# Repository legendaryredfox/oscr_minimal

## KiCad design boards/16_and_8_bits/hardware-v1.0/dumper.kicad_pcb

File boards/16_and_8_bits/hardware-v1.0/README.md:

# 16_and_8_bits v1.0

Versão **v1.0** da placa [`16_and_8_bits`](../README.md): shield 100% THT para Arduino Mega 2560 R3, só USB. Versão anterior, mantida ao lado da mais nova.

| | |
|---|---|
| Slots | SNES (62p), NES (72p), Famicom (60p), Mega Drive (64p), todos a 5 V, e GBA (32p, SMD, 1,5 mm) a 3,3 V (regulador U3) |
| Circuitos | Si5351 em header fêmea e PIC12F629 (CIC do SNES) em soquete. |
| Tamanho | 144,1 × 118,0 mm |
| Projeto KiCad | [`hardware-v1.0/`](.) (`dumper.kicad_pro`, `.kicad_sch`, `.kicad_pcb`) |
| Fábrica (JLCPCB) | `../fab/gerbers-v1.0/`, `../fab/dumper-v1.0-jlcpcb.zip` |
| Renders | `render-cima.png`, `render-baixo.png` |
| Estado | Nada montado nem testado com cartucho; revisar o layout no KiCad antes de encomendar |

## Troca de cartucho

O 5V dos slots vai direto do Mega e **não é cortado por software** (o desligamento por software foi retirado, D139). Para trocar o cartucho, **desligue a placa tirando o cabo USB** do Mega; nunca com a USB ligada.

## Proteção de corrente e tensão (D138)

**F1: fusível de vidro 5×20 mm de 500 mA (ação rápida) em suporte de clipes, opcional.** O suporte é de furo passante (Littelfuse série 100 ou equivalente) e o fusível queimado se troca **sem solda**; fica em série com o 5 V que a placa recebe do Mega Um curto no cartucho queima o fusível e protege a placa, o Mega e a porta USB. A queda é de 0,1 a 0,2 V a 200 mA (o SA-1 do SNES continua abaixo de ~5,2 V). **Sem o fusível no suporte a placa fica sem 5 V** (um fio no lugar dele também serve). Ele limita corrente e não protege contra tensão errada.

## Particularidades desta versão

Mínima que funciona, com o fusível F1 (D144).

## Lista de peças

| Referências | Valor | Footprint | Qtd |
|---|---|---|---|
| A1 | Mega2560_R3_Shield | `dumper:Mega2560_R3_Shield` | 1 |
| C1 | 470u/16V | `Capacitor_THT:CP_Radial_D8.0mm_P3.50mm` | 1 |
| C2,C3,C4,C5,C6,C9 | 100n | `Capacitor_THT:C_Disc_D5.0mm_W2.5mm_P5.00mm` | 6 |
| C7,C8 | 1u | `Capacitor_THT:C_Disc_D5.0mm_W2.5mm_P5.00mm` | 2 |
| D1 | LED 3mm | `LED_THT:LED_D3.0mm` | 1 |
| F1 | Fusivel 5x20 500mA | `Fuse:Fuseholder_Littelfuse_100_series_5x20mm` | 1 |
| FC1 | FC_Slot | `dumper:FC_Slot` | 1 |
| FLG1,FLG2 | PWR_FLAG | `` | 2 |
| GBA1 | GBA_Slot | `dumper:GBA_Slot` | 1 |
| MD1 | MD_Slot | `dumper:MD_Slot` | 1 |
| NES1 | NES_Slot | `dumper:NES_Slot` | 1 |
| R1 | 220R | `Resistor_THT:R_Axial_DIN0207_L6.3mm_D2.5mm_P10.16mm_Horizontal` | 1 |
| R2 | 1k | `Resistor_THT:R_Axial_DIN0207_L6.3mm_D2.5mm_P10.16mm_Horizontal` | 1 |
| SNES1 | SNES_Slot | `dumper:SNES_Slot` | 1 |
| U1 | Si5351_Module | `Connector_PinSocket_2.54mm:PinSocket_1x07_P2.54mm_Vertical` | 1 |
| U2 | PIC12F629 (snescic-lock-resync) | `Package_DIP:DIP-8_W7.62mm_Socket` | 1 |
| U3 | MCP1700-3302E/TO (3,3 V) | `Package_TO_SOT_THT:TO-92` | 1 |

Gerada do esquemático desta versão (`kicad-cli sch export bom`). Peças marcadas DNP ou opcionais: `docs/bom.md` da placa.

## Verificação e fábrica (da raiz do repositório)

```
python3 tools/check_netlist.py --board 16_and_8_bits boards/16_and_8_bits/hardware-v1.0/dumper.kicad_sch
kicad-cli sch erc boards/16_and_8_bits/hardware-v1.0/dumper.kicad_sch
kicad-cli pcb drc boards/16_and_8_bits/hardware-v1.0/dumper.kicad_pcb
tools/export_fab.sh 16_and_8_bits v1.0
tools/render_board.sh 16_and_8_bits v1.0 v1.1
```

Mais: [README da placa](../README.md), [`docs/`](../docs/).

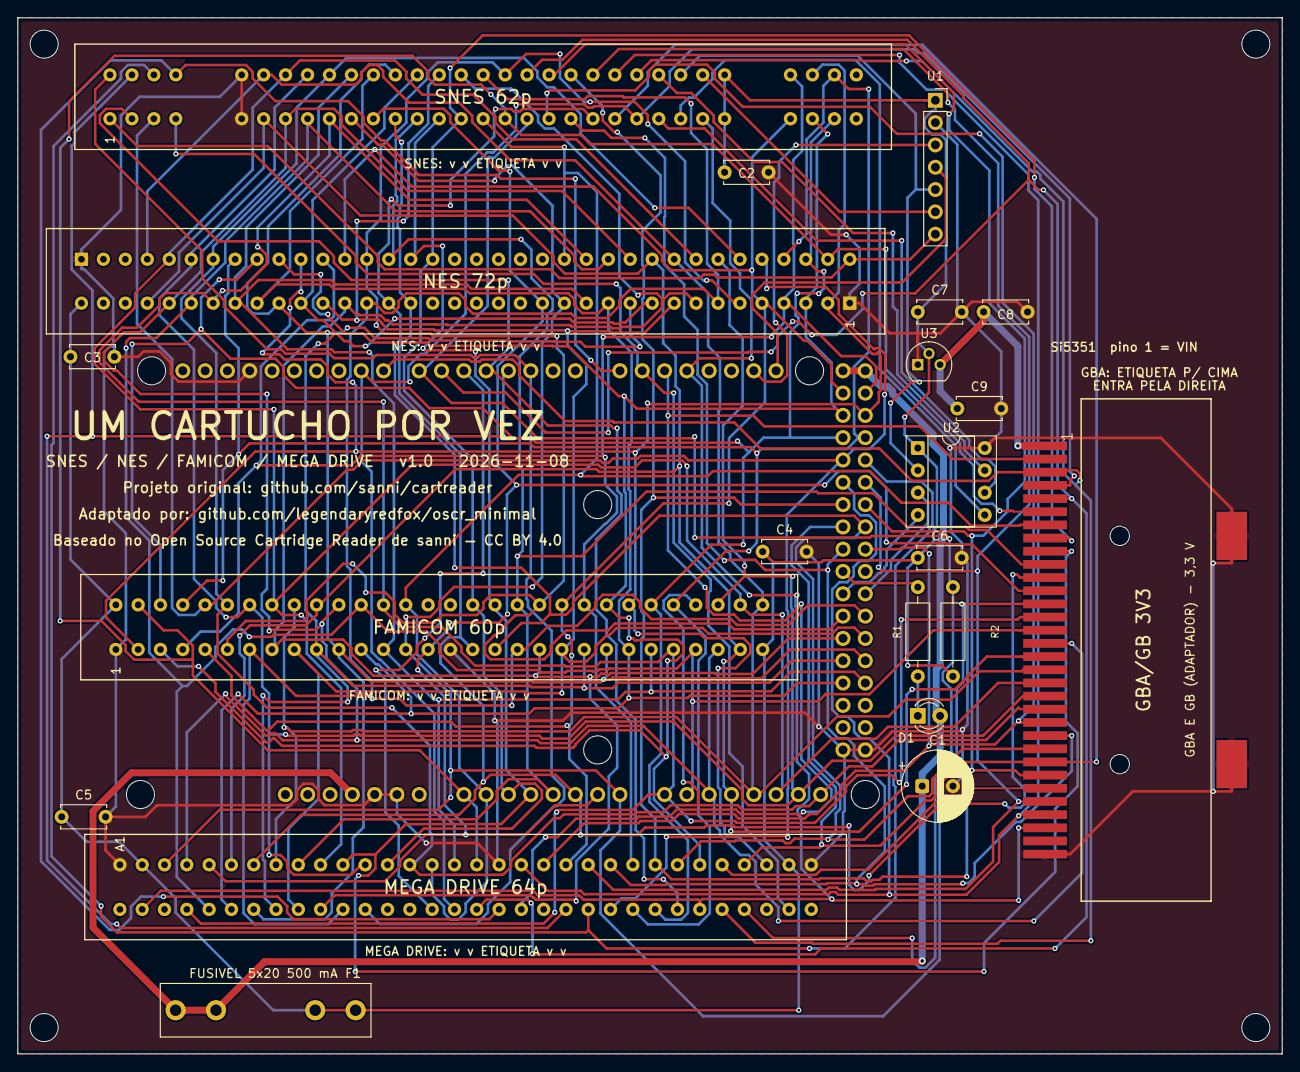
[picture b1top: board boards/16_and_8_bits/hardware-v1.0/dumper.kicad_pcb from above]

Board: 2 copper layers, 144.0 x 118.0 mm, 26 parts (0 on the bottom side), 68 nets.

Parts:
A1: Mega2560_R3_Shield
C1: 470u/16V; CP_Radial_D8.0mm_P3.50mm
C2, C3, C4, C5, C6, C9: 100n; C_Disc_D5.0mm_W2.5mm_P5.00mm
C7, C8: 1u; C_Disc_D5.0mm_W2.5mm_P5.00mm
D1: LED 3mm; LED_D3.0mm
F1: Fusivel 5x20 500mA; Fuseholder_Littelfuse_100_series_5x20mm
FC1: FC_Slot
GBA1: GBA_Slot
MD1: MD_Slot
MH1, MH2, MH3, MH4: MountingHole_3.2mm; MountingHole_3.2mm_M3
NES1: NES_Slot
R1: 220R; R_Axial_DIN0207_L6.3mm_D2.5mm_P10.16mm_Horizontal
R2: 1k; R_Axial_DIN0207_L6.3mm_D2.5mm_P10.16mm_Horizontal
SNES1: SNES_Slot
U1: Si5351_Module; PinSocket_1x07_P2.54mm_Vertical
U2: PIC12F629 (snescic-lock-resync); DIP-8_W7.62mm_Socket
U3: MCP1700-3302E/TO (3,3 V); TO-92

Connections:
+3V3: C8.1, C9.1, GBA1.1, U3.3
+5V: A1.5V1, A1.5V3, A1.5V4, C1.1, D1.2, F1.1
+5V_CART: C2.1, C3.1, C4.1, C5.1, C6.1, C7.1, F1.2, FC1.30, FC1.31, MD1.A2, MD1.A31, NES1.36, R2.1, SNES1.27, SNES1.58, U1.1, U2.1, U3.2
/A0: A1.A0, FC1.32, GBA1.6, MD1.A17, NES1.38, SNES1.17
/A1: A1.A1, FC1.44, GBA1.7, MD1.A15, NES1.50, SNES1.16
/A2: A1.A2, FC1.47, GBA1.8, MD1.A13, NES1.56, SNES1.15
/A3: A1.A3, FC1.48, GBA1.9, MD1.A11, NES1.57, SNES1.14
/A4: A1.A4, FC1.49, GBA1.10, MD1.A9, NES1.58, SNES1.13
/A5: A1.A5, FC1.17, GBA1.11, MD1.A7, NES1.21, SNES1.12
/A6: A1.A6, FC1.15, GBA1.12, MD1.A5, NES1.15, SNES1.11
/A7: A1.A7, FC1.14, GBA1.13, MD1.A3, NES1.14, SNES1.10
/A8: A1.A8, FC1.26, FC1.43, GBA1.14, MD1.B4, NES1.30, NES1.49, SNES1.9
/A9: A1.A9, FC1.27, FC1.42, GBA1.15, MD1.B5, NES1.31, NES1.48, SNES1.8
/A10: A1.A10, FC1.28, FC1.41, GBA1.16, MD1.A4, NES1.32, NES1.47, SNES1.7
/A11: A1.A11, FC1.29, FC1.40, GBA1.17, MD1.A6, NES1.33, NES1.46, SNES1.6
/A12: A1.A12, FC1.39, FC1.60, GBA1.18, MD1.A8, NES1.45, NES1.69, SNES1.37
/A13: A1.A13, FC1.38, FC1.59, GBA1.19, MD1.A10, NES1.44, NES1.68, SNES1.38
/A14: A1.A14, FC1.37, FC1.58, GBA1.20, MD1.A12, NES1.43, NES1.67, SNES1.39
/A15: A1.A15, FC1.36, FC1.57, GBA1.21, MD1.A14, NES1.42, NES1.66, SNES1.40
/CIC_DATA_0: SNES1.55, U2.7
/CIC_DATA_1: SNES1.24, U2.6
/CIC_RESET: SNES1.25, U2.5
/CLK0: NES1.37, SNES1.1, U1.7
/CLK1: SNES1.57, U1.6
/CLK2: SNES1.56, U1.5, U2.2
/D2: A1.D2, MD1.B12, SNES1.32
/D3: A1.D3, MD1.B21, SNES1.33
/D4: A1.D4, MD1.B26, SNES1.2
/D5: A1.D5, MD1.B15
/D6: A1.D6, GBA1.5, MD1.B17, SNES1.49
/D7: A1.D7, MD1.B29, R2.2, SNES1.18
/D8: A1.D8, GBA1.3, MD1.B28, SNES1.54
/D9: A1.D9, GBA1.4, MD1.B16, SNES1.23
/D14: A1.D14, MD1.B18, SNES1.35
/D15: A1.D15, MD1.B31, SNES1.4
/D16: A1.D16, GBA1.2, MD1.B19
/D17: A1.D17, GBA1.30, MD1.B2, MD1.B27, SNES1.26
/D22: A1.D22, FC1.5, FC1.51, MD1.A21, NES1.5, NES1.60, SNES1.28
/D23: A1.D23, FC1.4, FC1.52, MD1.A24, NES1.4, NES1.61, SNES1.59
/D24: A1.D24, FC1.3, FC1.53, MD1.A27, NES1.3, NES1.63, SNES1.29
/D25: A1.D25, FC1.2, FC1.54, MD1.A30, NES1.2, NES1.62, SNES1.60
/D26: A1.D26, FC1.33, FC1.55, MD1.B25, NES1.39, NES1.64, SNES1.30
/D27: A1.D27, FC1.34, FC1.56, MD1.B24, NES1.40, NES1.65, SNES1.61
/D28: A1.D28, FC1.35, MD1.B23, NES1.41, SNES1.3
/D29: A1.D29, MD1.B22, SNES1.34
/D30: A1.D30, GBA1.29, MD1.A19, SNES1.53
/D31: A1.D31, GBA1.28, MD1.A22, SNES1.52
/D32: A1.D32, GBA1.27, MD1.A25, SNES1.51
/D33: A1.D33, GBA1.26, MD1.A28, SNES1.50
/D34: A1.D34, GBA1.25, MD1.A29, SNES1.22
/D35: A1.D35, FC1.18, GBA1.24, MD1.A26, NES1.22, SNES1.21
/D36: A1.D36, GBA1.23, MD1.A23, SNES1.20
/D37: A1.D37, GBA1.22, MD1.A20, SNES1.19
/D42: A1.D42, FC1.6, FC1.50, NES1.6, NES1.59, SNES1.48
/D43: A1.D43, FC1.7, FC1.19, MD1.B11, NES1.7, NES1.23, SNES1.47
/D44: A1.D44, FC1.8, FC1.20, MD1.B10, NES1.8, NES1.24, SNES1.46
/D45: A1.D45, FC1.9, FC1.21, MD1.B9, NES1.9, NES1.25, SNES1.45
/D46: A1.D46, FC1.10, FC1.22, MD1.B8, NES1.10, NES1.26, SNES1.44
/D47: A1.D47, FC1.11, FC1.23, MD1.B7, NES1.11, NES1.27, SNES1.43
/D48: A1.D48, FC1.12, FC1.24, MD1.B6, NES1.12, NES1.28, SNES1.42
/D49: A1.D49, FC1.13, FC1.25, MD1.A16, NES1.13, NES1.29, SNES1.41
GND: A1.GND1, A1.GND2, A1.GND3, A1.GND5, A1.GND6, C1.2, C2.2, C3.2, C4.2, C5.2, C6.2, C7.2, C8.2, C9.2, FC1.1, FC1.16, GBA1.32, GBA1.SHIELD_3, GBA1.SHIELD_4, MD1.A1, MD1.A18, MD1.A32, NES1.1, NES1.72, SNES1.5, SNES1.36, U1.2, U2.8, U3.1
unnamed: A1.D38, R1.2
unnamed: D1.1, R1.1
unnamed: A1.D21, U1.4
unnamed: A1.D20, U1.3
unnamed: A1.D40, U2.4
unnamed: A1.D41, U2.3

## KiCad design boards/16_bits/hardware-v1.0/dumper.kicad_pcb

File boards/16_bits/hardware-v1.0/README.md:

# 16_bits v1.0

Versão **v1.0** da placa [`16_bits`](../README.md): shield 100% THT para Arduino Mega 2560 R3, só USB. Versão anterior, mantida ao lado da mais nova.

| | |
|---|---|
| Slots | SNES (62p) e Mega Drive (64p), 5 V |
| Circuitos | Si5351 em header fêmea e PIC12F629 (CIC do SNES) em soquete. Sem botão de reset em nenhuma versão (D128). |
| Tamanho | 108,1 × 86,1 mm |
| Projeto KiCad | [`hardware-v1.0/`](.) (`dumper.kicad_pro`, `.kicad_sch`, `.kicad_pcb`) |
| Fábrica (JLCPCB) | `../fab/gerbers-v1.0/`, `../fab/dumper-v1.0-jlcpcb.zip` |
| Renders | `render-cima.png`, `render-baixo.png` |
| Proteção | F1: suporte de fusível 5×20 mm, 500 mA, em série com o 5 V dos slots (acrescentado em 2026-11-09, D144) |
| Estado | A placa encomendada (gerbers de 2026-11-03, sem o F1) chegou e foi montada em 2026-11-27: encaixe no Mega e footprints dos slots SNES e Mega Drive conferidos pelo usuário (D233). Teste elétrico e com cartucho ainda não feitos |

## Troca de cartucho

O 5V dos slots vai direto do Mega e **não é cortado por software** (o desligamento por software foi retirado, D139). Para trocar o cartucho, **desligue a placa tirando o cabo USB** do Mega; nunca com a USB ligada.

## F1 (D144)

**F1: fusível de vidro 5×20 mm de 500 mA (ação rápida) em suporte de clipes, de furo passante** (Littelfuse série 100 ou equivalente). Fica em série entre o 5 V do Mega e o `+5V_CART` (slots, Si5351, PIC, R2 e capacitores): um curto no cartucho queima o fusível e protege a placa, o Mega e a porta USB. O fusível queimado se troca **sem solda**. **Sem o fusível no suporte a placa fica sem 5 V** (um fio no lugar também serve). Limita corrente; não protege contra tensão errada. Posição: canto de cima, à direita do Si5351, sem aumentar a placa (108,1 × 86,1 mm). **As placas v1.0 já encomendadas em 2026-11-06 não têm o F1**; estes arquivos valem para uma nova encomenda.

## Particularidades desta versão

Antiga `rev2` (D97): alimentação em 0,8 mm, sem resistores série nem TVS nas linhas de controle, sem `/CART` no D50, sem C5, C6 e pontos de teste, sem furos M3 do Mega. A v1.0 original (trilhas de 0,3 mm) foi encomendada pelo usuário em 2026-11-06 e seus gerbers saíram do repositório (D110).

## Lista de peças

| Referências | Valor | Footprint | Qtd |
|---|---|---|---|
| A1 | Mega2560_R3_Shield | `dumper:Mega2560_R3_Shield` | 1 |
| C1 | 470u/16V | `Capacitor_THT:CP_Radial_D8.0mm_P3.50mm` | 1 |
| C2,C3,C4 | 100n | `Capacitor_THT:C_Disc_D5.0mm_W2.5mm_P5.00mm` | 3 |
| D1 | LED 3mm | `LED_THT:LED_D3.0mm` | 1 |
| FLG1,FLG2 | PWR_FLAG | `` | 2 |
| MD1 | MD_Slot | `dumper:MD_Slot` | 1 |
| F1 | Fusivel 5x20 500mA | `Fuse:Fuseholder_Littelfuse_100_series_5x20mm` | 1 |
| R1 | 220R | `Resistor_THT:R_Axial_DIN0207_L6.3mm_D2.5mm_P10.16mm_Horizontal` | 1 |
| R2 | 1k | `Resistor_THT:R_Axial_DIN0207_L6.3mm_D2.5mm_P10.16mm_Horizontal` | 1 |
| SNES1 | SNES_Slot | `dumper:SNES_Slot` | 1 |
| U1 | Si5351_Module | `Connector_PinSocket_2.54mm:PinSocket_1x07_P2.54mm_Vertical` | 1 |
| U2 | PIC12F629 (em soquete; snescic-lock-resync) | `Package_DIP:DIP-8_W7.62mm` | 1 |

Gerada do esquemático desta versão (`kicad-cli sch export bom`). Peças marcadas DNP ou opcionais: `docs/bom.md` da placa.

## Verificação e fábrica (da raiz do repositório)

```
kicad-cli sch erc boards/16_bits/hardware-v1.0/dumper.kicad_sch
kicad-cli pcb drc boards/16_bits/hardware-v1.0/dumper.kicad_pcb
tools/export_fab.sh 16_bits v1.0
tools/render_board.sh 16_bits v1.0 v1.2 v1.3
```

`tools/check_netlist.py` não se aplica à v1.0 da `16_bits`: o `pinmap.md` atual inclui C5, C6, D3 a D14 e TP2, que esta versão não tem.

Mais: [README da placa](../README.md), [`docs/`](../docs/). Comparação entre as versões: [`docs/versoes.md`](../docs/versoes.md).

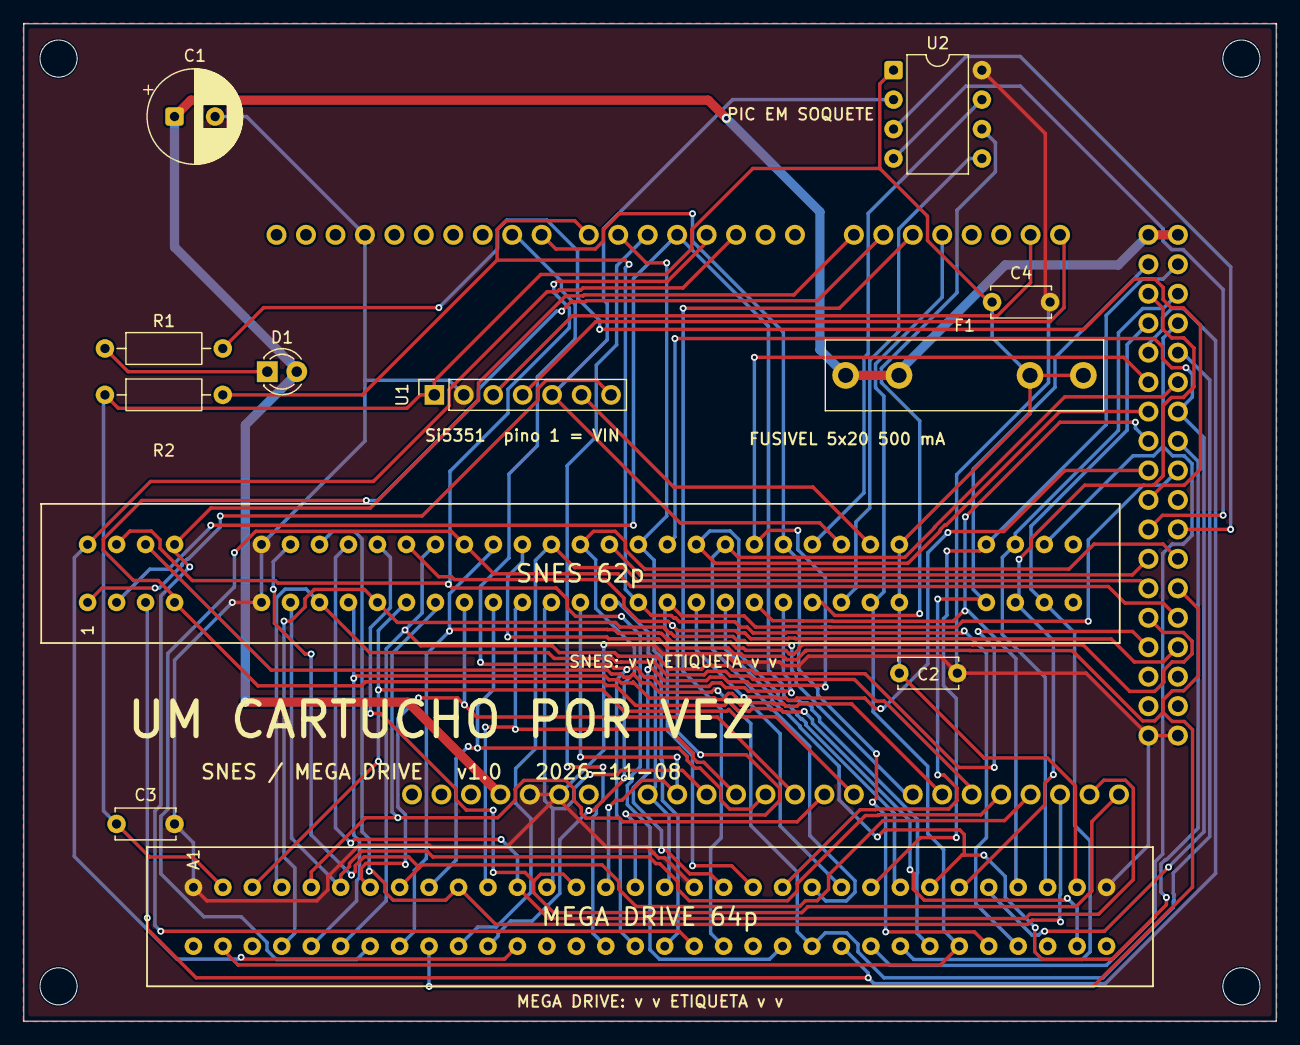
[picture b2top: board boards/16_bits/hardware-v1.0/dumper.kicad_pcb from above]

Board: 2 copper layers, 108.0 x 86.0 mm, 17 parts (0 on the bottom side), 67 nets.

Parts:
A1: Mega2560_R3_Shield
C1: 470u/16V; CP_Radial_D8.0mm_P3.50mm
C2, C3, C4: 100n; C_Disc_D5.0mm_W2.5mm_P5.00mm
D1: LED 3mm; LED_D3.0mm
F1: Fusivel 5x20 500mA; Fuseholder_Littelfuse_100_series_5x20mm
MD1: MD_Slot
MH1, MH2, MH3, MH4: MountingHole_3.2mm; MountingHole_3.2mm_M3
R1: 220R; R_Axial_DIN0207_L6.3mm_D2.5mm_P10.16mm_Horizontal
R2: 1k; R_Axial_DIN0207_L6.3mm_D2.5mm_P10.16mm_Horizontal
SNES1: SNES_Slot
U1: Si5351_Module; PinSocket_1x07_P2.54mm_Vertical
U2: PIC12F629 (em soquete; snescic-lock-resync); DIP-8_W7.62mm

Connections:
+5V: A1.5V1, A1.5V3, A1.5V4, C1.1, D1.2, F1.1
+5V_CART: C2.1, C3.1, C4.1, F1.2, MD1.A2, MD1.A31, R2.1, SNES1.27, SNES1.58, U1.1, U2.1
/A0: A1.A0, MD1.A17, SNES1.17
/A1: A1.A1, MD1.A15, SNES1.16
/A2: A1.A2, MD1.A13, SNES1.15
/A3: A1.A3, MD1.A11, SNES1.14
/A4: A1.A4, MD1.A9, SNES1.13
/A5: A1.A5, MD1.A7, SNES1.12
/A6: A1.A6, MD1.A5, SNES1.11
/A7: A1.A7, MD1.A3, SNES1.10
/A8: A1.A8, MD1.B4, SNES1.9
/A9: A1.A9, MD1.B5, SNES1.8
/A10: A1.A10, MD1.A4, SNES1.7
/A11: A1.A11, MD1.A6, SNES1.6
/A12: A1.A12, MD1.A8, SNES1.37
/A13: A1.A13, MD1.A10, SNES1.38
/A14: A1.A14, MD1.A12, SNES1.39
/A15: A1.A15, MD1.A14, SNES1.40
/CIC_DATA_0: SNES1.55, U2.7
/CIC_DATA_1: SNES1.24, U2.6
/CIC_RESET: SNES1.25, U2.5
/CLK0: SNES1.1, U1.7
/CLK1: SNES1.57, U1.6
/CLK2: SNES1.56, U1.5, U2.2
/D2: A1.D2, MD1.B12, SNES1.32
/D3: A1.D3, MD1.B21, SNES1.33
/D4: A1.D4, MD1.B26, SNES1.2
/D5: A1.D5, MD1.B15
/D6: A1.D6, MD1.B17, SNES1.49
/D7: A1.D7, MD1.B29, R2.2, SNES1.18
/D8: A1.D8, MD1.B28, SNES1.54
/D9: A1.D9, MD1.B16, SNES1.23
/D14: A1.D14, MD1.B18, SNES1.35
/D15: A1.D15, MD1.B31, SNES1.4
/D16: A1.D16, MD1.B19
/D17: A1.D17, MD1.B2, MD1.B27, SNES1.26
/D22: A1.D22, MD1.A21, SNES1.28
/D23: A1.D23, MD1.A24, SNES1.59
/D24: A1.D24, MD1.A27, SNES1.29
/D25: A1.D25, MD1.A30, SNES1.60
/D26: A1.D26, MD1.B25, SNES1.30
/D27: A1.D27, MD1.B24, SNES1.61
/D28: A1.D28, MD1.B23, SNES1.3
/D29: A1.D29, MD1.B22, SNES1.34
/D30: A1.D30, MD1.A19, SNES1.53
/D31: A1.D31, MD1.A22, SNES1.52
/D32: A1.D32, MD1.A25, SNES1.51
/D33: A1.D33, MD1.A28, SNES1.50
/D34: A1.D34, MD1.A29, SNES1.22
/D35: A1.D35, MD1.A26, SNES1.21
/D36: A1.D36, MD1.A23, SNES1.20
/D37: A1.D37, MD1.A20, SNES1.19
/D42: A1.D42, SNES1.48
/D43: A1.D43, MD1.B11, SNES1.47
/D44: A1.D44, MD1.B10, SNES1.46
/D45: A1.D45, MD1.B9, SNES1.45
/D46: A1.D46, MD1.B8, SNES1.44
/D47: A1.D47, MD1.B7, SNES1.43
/D48: A1.D48, MD1.B6, SNES1.42
/D49: A1.D49, MD1.A16, SNES1.41
GND: A1.GND1, A1.GND2, A1.GND3, A1.GND5, A1.GND6, C1.2, C2.2, C3.2, C4.2, MD1.A1, MD1.A18, MD1.A32, SNES1.5, SNES1.36, U1.2, U2.8
unnamed: A1.D38, R1.2
unnamed: D1.1, R1.1
unnamed: A1.D21, U1.4
unnamed: A1.D20, U1.3
unnamed: A1.D40, U2.4
unnamed: A1.D41, U2.3

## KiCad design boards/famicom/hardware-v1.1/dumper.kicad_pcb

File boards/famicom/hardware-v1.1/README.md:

# famicom v1.1

Versão **v1.1** da placa [`famicom`](../README.md): shield 100% THT para Arduino Mega 2560 R3, só USB. Esta é a versão mais nova.

| | |
|---|---|
| Slots | Famicom (60p, 2,54 mm), 5 V |
| Circuitos | Sem Si5351 e sem PIC. |
| Tamanho | 107,1 × 105,1 mm |
| Projeto KiCad | [`hardware-v1.1/`](.) (`dumper.kicad_pro`, `.kicad_sch`, `.kicad_pcb`) |
| Fábrica (JLCPCB) | `../fab/gerbers-v1.1/`, `../fab/dumper-v1.1-jlcpcb.zip` |
| Renders | `render-cima.png`, `render-baixo.png` |
| Estado | Nada montado nem testado com cartucho; revisar o layout no KiCad antes de encomendar |

## Troca de cartucho

O 5V dos slots vai direto do Mega e **não é cortado por software** (o desligamento por software foi retirado, D139). Para trocar o cartucho, **desligue a placa tirando o cabo USB** do Mega; nunca com a USB ligada.

## Proteção de corrente e tensão (D138)

**F1: fusível de vidro 5×20 mm de 500 mA (ação rápida) em suporte de clipes, opcional.** O suporte é de furo passante (Littelfuse série 100 ou equivalente) e o fusível queimado se troca **sem solda**; fica em série com o 5 V que a placa recebe do Mega Um curto no cartucho queima o fusível e protege a placa, o Mega e a porta USB. A queda é de 0,1 a 0,2 V a 200 mA (o SA-1 do SNES continua abaixo de ~5,2 V). **Sem o fusível no suporte a placa fica sem 5 V** (um fio no lugar dele também serve). Ele limita corrente e não protege contra tensão errada.

**Seletor de tensão 3,3 V/5 V dos slots Famicom** (LDO LD1117V33 em TO-220, Q4 de bypass, Q5 de carga, comando no D18; sem resistores em série entre o Mega e os slots, D140). **Padrão: 5 V**; 3,3 V só quando o usuário pede (`--voltage 3v3`, ou o botão da GUI). Passar de 3,3 V para 5 V mostra um alerta e pede confirmação. Os outros slots e o Si5351/PIC ficam direto no 5 V. Cartuchos de 3,3 V ligados em 5 V podem queimar, e em 3,3 V as saídas do Mega continuam em 5 V: **confira a tensão que o cartucho suporta antes de inserir**.

**J1: jumper "TRAVA 3,3 V", opcional.** Fechado, prende o gate do Q4 no 5 V e o slot nunca passa de 3,3 V, mesmo com erro de software ou de GUI: é a única defesa independente do firmware. Aberto, o seletor funciona normalmente.

## O que muda em relação à v1.0

| Peça | Referências | Antes | Agora |
|---|---|---|---|
| 10u/16V | C4 | 0 | 1 |
| TRAVA 3,3 V | J1 | 0 | 1 |
| IRF9540N | Q4 | 0 | 1 |
| 2N7000 | Q5 | 0 | 1 |
| 100k | R9 | 0 | 1 |
| 1k | R10 | 0 | 1 |
| 220R | R11 | 0 | 1 |
| LD1117V33 | U1 | 0 | 1 |
| 100n | C2,C3 | 1 | 2 |

## Lista de peças

| Referências | Valor | Footprint | Qtd |
|---|---|---|---|
| A1 | Mega2560_R3_Shield | `dumper:Mega2560_R3_Shield` | 1 |
| C1 | 470u/16V | `Capacitor_THT:CP_Radial_D8.0mm_P3.50mm` | 1 |
| C2,C3 | 100n | `Capacitor_THT:C_Disc_D5.0mm_W2.5mm_P5.00mm` | 2 |
| C4 | 10u/16V | `Capacitor_THT:CP_Radial_D5.0mm_P2.00mm` | 1 |
| D1 | LED 3mm | `LED_THT:LED_D3.0mm` | 1 |
| F1 | Fusivel 5x20 500mA | `Fuse:Fuseholder_Littelfuse_100_series_5x20mm` | 1 |
| FC1 | FC_Slot | `dumper:FC_Slot` | 1 |
| FLG1,FLG2 | PWR_FLAG | `` | 2 |
| J1 | TRAVA 3,3 V | `Connector_PinHeader_2.54mm:PinHeader_1x02_P2.54mm_Vertical` | 1 |
| Q4 | IRF9540N | `Package_TO_SOT_THT:TO-220-3_Vertical` | 1 |
| Q5 | 2N7000 | `Package_TO_SOT_THT:TO-92_Inline` | 1 |
| R1 | 220R | `Resistor_THT:R_Axial_DIN0207_L6.3mm_D2.5mm_P10.16mm_Horizontal` | 1 |
| R9 | 100k | `Resistor_THT:R_Axial_DIN0204_L3.6mm_D1.6mm_P2.54mm_Vertical` | 1 |
| R10 | 1k | `Resistor_THT:R_Axial_DIN0204_L3.6mm_D1.6mm_P2.54mm_Vertical` | 1 |
| R11 | 220R | `Resistor_THT:R_Axial_DIN0204_L3.6mm_D1.6mm_P2.54mm_Vertical` | 1 |
| U1 | LD1117V33 | `Package_TO_SOT_THT:TO-220-3_Vertical` | 1 |

Gerada do esquemático desta versão (`kicad-cli sch export bom`). Peças marcadas DNP ou opcionais: `docs/bom.md` da placa.

## Verificação e fábrica (da raiz do repositório)

```
python3 tools/check_netlist.py --board famicom boards/famicom/hardware-v1.1/dumper.kicad_sch
kicad-cli sch erc boards/famicom/hardware-v1.1/dumper.kicad_sch
kicad-cli pcb drc boards/famicom/hardware-v1.1/dumper.kicad_pcb
tools/export_fab.sh famicom v1.1
tools/render_board.sh famicom v1.0 v1.1
```

Mais: [README da placa](../README.md), [`docs/`](../docs/).

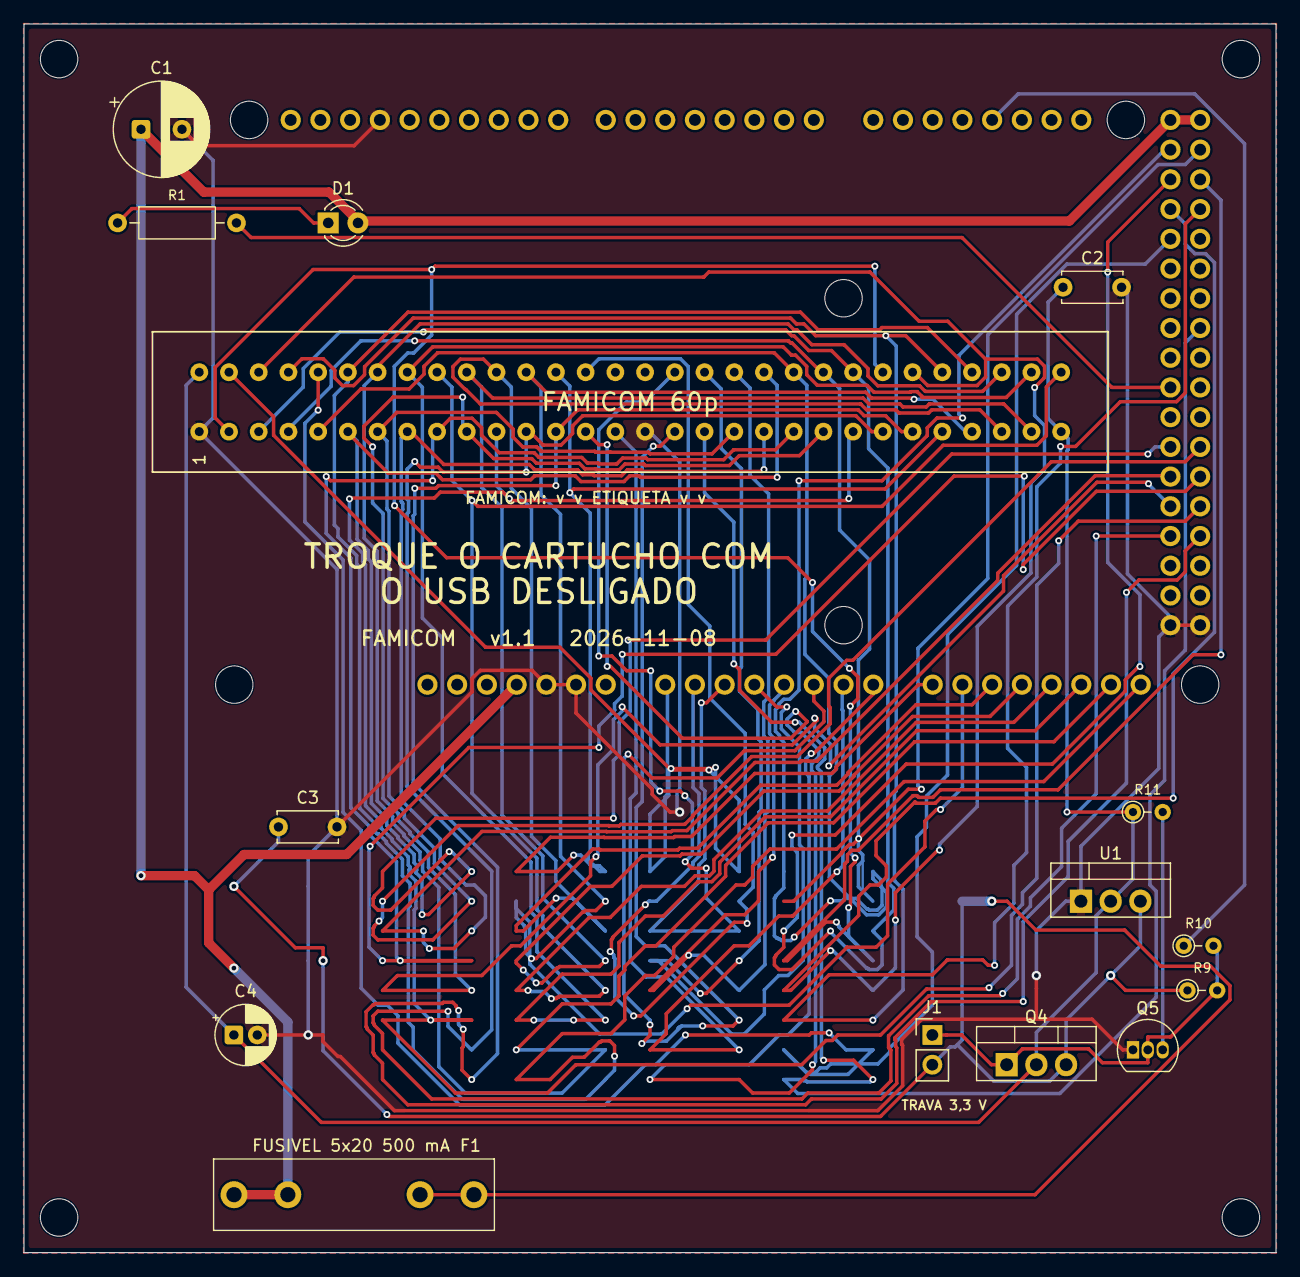
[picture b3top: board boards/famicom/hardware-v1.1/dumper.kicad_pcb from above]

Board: 2 copper layers, 107.0 x 105.0 mm, 20 parts (0 on the bottom side), 41 nets.

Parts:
A1: Mega2560_R3_Shield
C1: 470u/16V; CP_Radial_D8.0mm_P3.50mm
C2, C3: 100n; C_Disc_D5.0mm_W2.5mm_P5.00mm
C4: 10u/16V; CP_Radial_D5.0mm_P2.00mm
D1: LED 3mm; LED_D3.0mm
F1: Fusivel 5x20 500mA; Fuseholder_Littelfuse_100_series_5x20mm
FC1: FC_Slot
J1: TRAVA 3,3 V; PinHeader_1x02_P2.54mm_Vertical
MH1, MH2, MH3, MH4: MountingHole_3.2mm; MountingHole_3.2mm_M3
Q4: IRF9540N; TO-220-3_Vertical
Q5: 2N7000; TO-92_Inline
R1: 220R; R_Axial_DIN0207_L6.3mm_D2.5mm_P10.16mm_Horizontal
R9: 100k; R_Axial_DIN0204_L3.6mm_D1.6mm_P2.54mm_Vertical
R10: 1k; R_Axial_DIN0204_L3.6mm_D1.6mm_P2.54mm_Vertical
R11: 220R; R_Axial_DIN0204_L3.6mm_D1.6mm_P2.54mm_Vertical
U1: LD1117V33; TO-220-3_Vertical

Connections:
+5V: A1.5V1, A1.5V3, A1.5V4, C1.1, D1.2, F1.1
+5V_CART: C3.1, F1.2, J1.2, Q4.3, R9.1, U1.3
/A0: A1.A0, FC1.32
/A1: A1.A1, FC1.44
/A2: A1.A2, FC1.47
/A3: A1.A3, FC1.48
/A4: A1.A4, FC1.49
/A5: A1.A5, FC1.17
/A6: A1.A6, FC1.15
/A7: A1.A7, FC1.14
/A8: A1.A8, FC1.26, FC1.43
/A9: A1.A9, FC1.27, FC1.42
/A10: A1.A10, FC1.28, FC1.41
/A11: A1.A11, FC1.29, FC1.40
/A12: A1.A12, FC1.39, FC1.60
/A13: A1.A13, FC1.38, FC1.59
/A14: A1.A14, FC1.37, FC1.58
/A15: A1.A15, FC1.36, FC1.57
/D22: A1.D22, FC1.5, FC1.51
/D23: A1.D23, FC1.4, FC1.52
/D24: A1.D24, FC1.3, FC1.53
/D25: A1.D25, FC1.2, FC1.54
/D26: A1.D26, FC1.33, FC1.55
/D27: A1.D27, FC1.34, FC1.56
/D28: A1.D28, FC1.35
/D35: A1.D35, FC1.18
/D42: A1.D42, FC1.6, FC1.50
/D43: A1.D43, FC1.7, FC1.19
/D44: A1.D44, FC1.8, FC1.20
/D45: A1.D45, FC1.9, FC1.21
/D46: A1.D46, FC1.10, FC1.22
/D47: A1.D47, FC1.11, FC1.23
/D48: A1.D48, FC1.12, FC1.24
/D49: A1.D49, FC1.13, FC1.25
/VSEL_EN: A1.D18, R10.1
/VSEL_G: J1.1, Q4.1, Q5.2, R9.2, R10.2
GND: A1.GND1, A1.GND2, A1.GND3, A1.GND5, A1.GND6, C1.2, C2.2, C3.2, C4.2, FC1.1, FC1.16, Q5.1, U1.1
unnamed: A1.D38, R1.2
unnamed: D1.1, R1.1
unnamed: Q5.3, R11.2
VCC_CART: C2.1, C4.1, FC1.30, FC1.31, Q4.2, R11.1, U1.2

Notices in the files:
boards/16_and_8_bits/hardware-v1.0/dumper.kicad_pcb:
Baseado no Open Source Cartridge Reader de sanni — CC BY 4.0
